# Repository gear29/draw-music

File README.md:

# draw-music
The music drawing device
This will hold a pcb that will have two sider one that controls volume and one that controls frequency making it so that when connected at 90 deg they can act like a coordinate system making it so when you slide them to find a coordinate on the grid it will emulate a sound. The pcb will be held in a 3d printed case so it can also hold paper and have the 2 sliders connected where a pen can rest so when you draw on the paper it makes music. IT will not need any computing power since the pcb dose all the procesing for the sound manuly and makes it just by using a vco (voltage controled oscillator) and a volume module making it so it can make the sound with almost no hesitation.

BOM
"Reference","Qty","Value","DNP","Exclude from BOM","Exclude from Board","Footprint","Datasheet"
"10nf1,10nF3,220µF1","3","C","","","","Capacitor_SMD:CP_Elec_3x5.3","~"
"10nf2,10nf4","2","R_Potentiometer","","","","Potentiometer_THT:Potentiometer_Bourns_PTA6043_Single_Slide","~"
"10nF5","1","Timeing cap","","","","Capacitor_SMD:CP_Elec_3x5.3","~"
"LS1","1","Speaker","","","","Buzzer_Beeper:Speaker_CUI_CMR-1206S-67","~"
"R1","1","R","","","","Resistor_SMD:R_0201_0603Metric","~"
"U1","1","LM555xM","","","","Package_SO:SOIC-8_3.9x4.9mm_P1.27mm","http://www.ti.com/lit/ds/symlink/lm555.pdf"
"U2","1","volume incres","","","","Package_DIP:DIP-8_W7.62mm","http://www.ti.com/lit/ds/symlink/lm386.pdf"

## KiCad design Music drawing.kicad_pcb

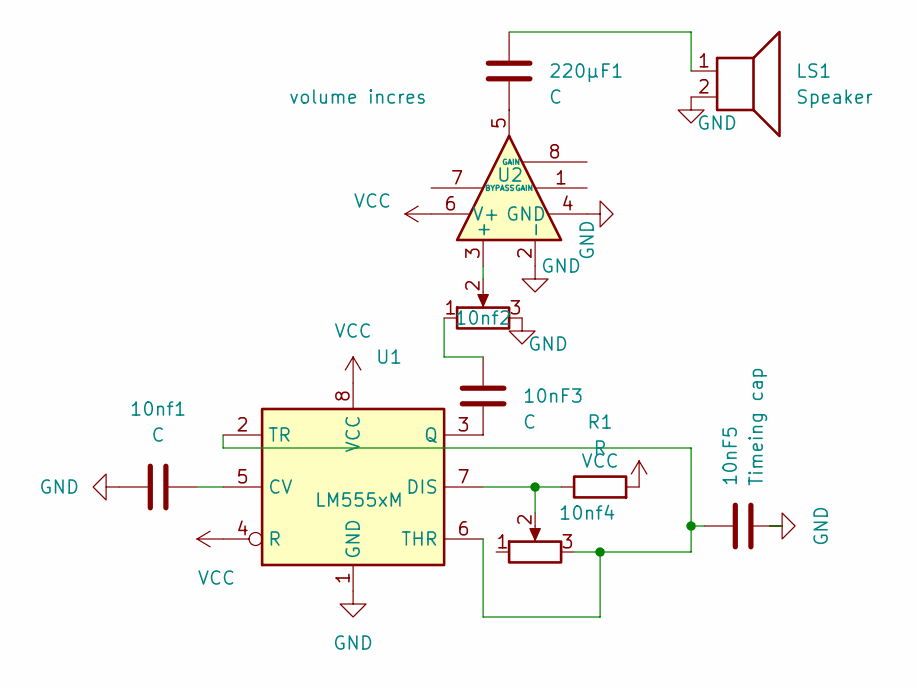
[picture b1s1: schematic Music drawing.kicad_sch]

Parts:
10nF3, 10nf1, 220µF1: C; CP_Elec_3x5.3
10nF5: Timeing cap; CP_Elec_3x5.3
10nf2, 10nf4: R_Potentiometer; Potentiometer_Bourns_PTA6043_Single_Slide
LS1: Speaker; Speaker_CUI_CMR-1206S-67
R1: R; R_0201_0603Metric
U1: LM555xM; SOIC-8_3.9x4.9mm_P1.27mm
U2: volume incres; DIP-8_W7.62mm

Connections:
GND: 10nF5.2, 10nf1.1, 10nf2.3, LS1.2, U1.1 (GND), U2.2 (-), U2.4 (GND)
unnamed: 10nF3.2, 10nf2.1
unnamed: 220µF1.1, U2.5
unnamed: 220µF1.2, LS1.1
unnamed: 10nf1.2, U1.5 (CV)
unnamed: 10nf4.2, R1.1, U1.7 (DIS)
unnamed: 10nF3.1, U1.3 (Q)
unnamed: 10nF5.1, 10nf4.3, U1.2 (TR), U1.6 (THR)
unnamed: 10nf2.2, U2.3 (+)
VCC: R1.2, U1.4 (R), U1.8 (VCC), U2.6 (V+)

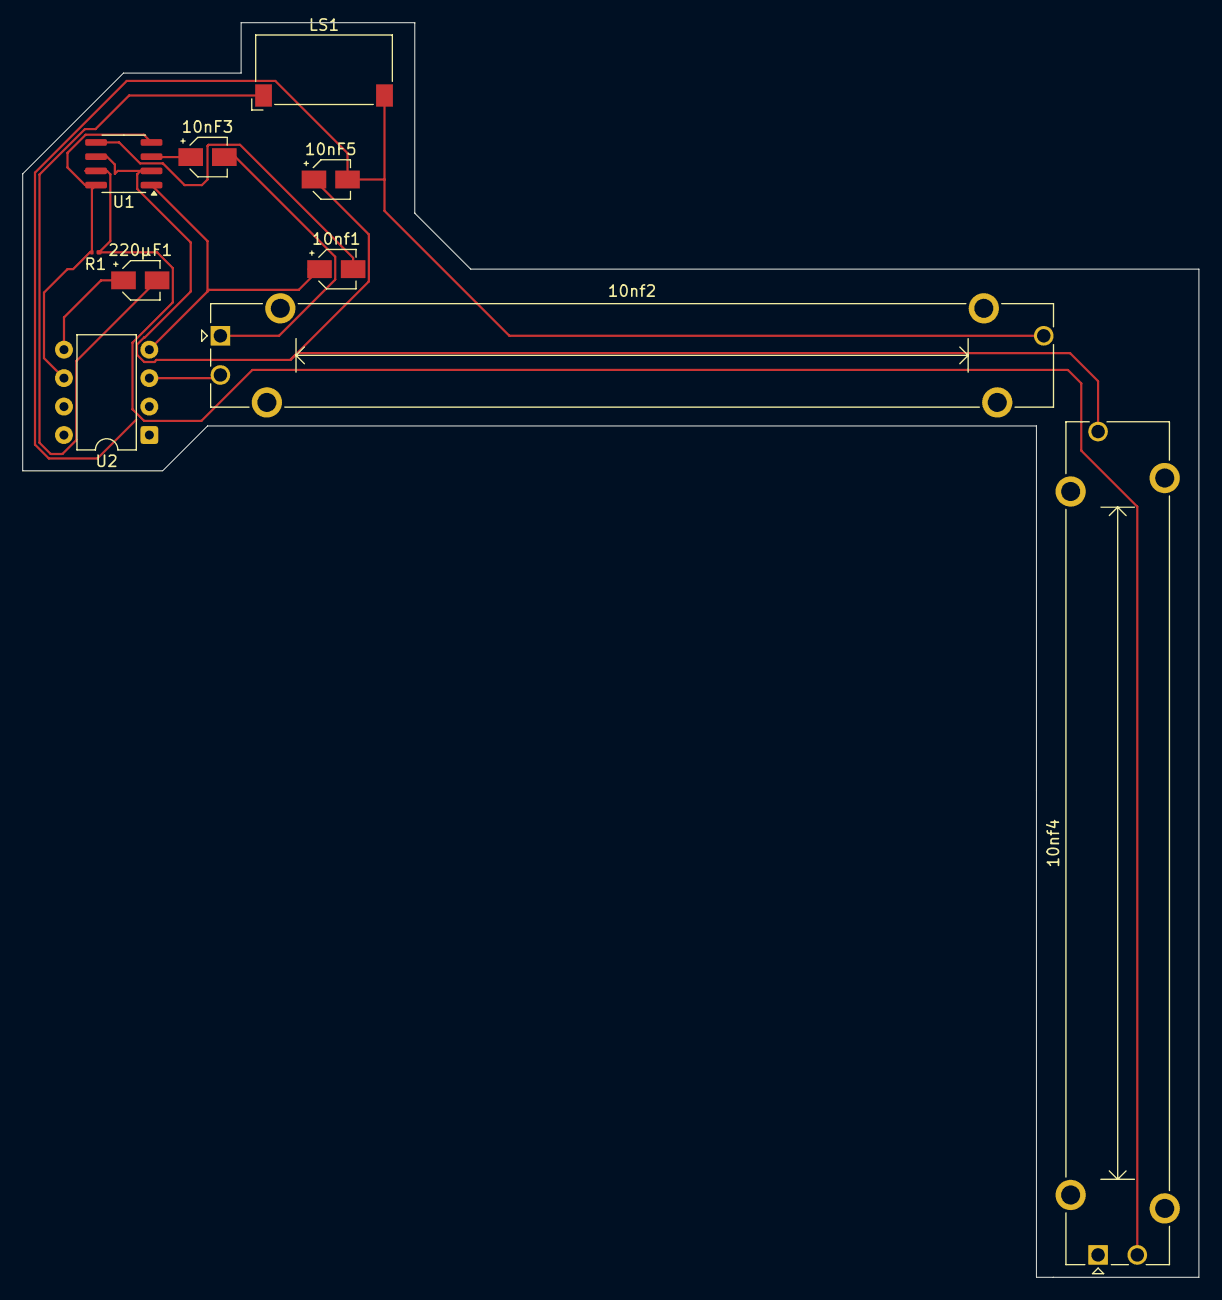
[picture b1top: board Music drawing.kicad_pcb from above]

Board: 2 copper layers, 105.0 x 112.0 mm, 10 parts (0 on the bottom side), 10 nets.
